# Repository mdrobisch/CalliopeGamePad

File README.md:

# CalliopeGamePad

The CalliopeGamePad adds a gamepad to the Calliope Mini V3 (https://calliope.cc/).
This project is a open source hardware project made with KiCAD (https://www.kicad.org/).
It is intended to be 100% compatible with the CallioGamer of M. Klein @ https://www.hackster.io/MKlein/calliogamer-f57906 . Thanks goes to M. Klein for his wonderful project and his software @ https://github.com/MKleinSB/pxt-calliogamer.

ATTENTION: Due to the connector the Calliope Game Pad Works **only** with Calliope Mini V3.

Here are some differeneces compared to the CallioGamer:

* The CallioGamer production files seems to be broken somehow (at least for my PCB fab of choice). Now you have the freedom to adjust for yours as well.
* Added some additional mounting holes. So you can add a solid body to the board (e.g., cardboard or 3d-print)
* Optional Pull-Up resistors are available. This can also be used for filtering of the buttons with additional capacitors. There is **no need** to solder this for a working gamepad.
* CalliopeGamePad is made in KiCAD 9 (instead of EasyEDA)

You can remix the project and adjust as you like. The hardware is licensed under Creative Commons (CC BY-SA). Please visit the projects of M.Klein and have fun.

## Build your own

Almost all of the big PCB Fabs are able to handle.kicad_pcb files directly. Just upload and let them produce your Calliope Game Pad. In addition you find the gerber fabrication files in the `gerber` directory.

## Software

Please follow the instruction at https://www.hackster.io/MKlein/calliogamer-f57906 . 

You can find the source code of the CallioGamer firmware at https://github.com/MKleinSB/pxt-calliogamer .

## Legal statement

Please read the DISCLAIMER and the LICENSE.

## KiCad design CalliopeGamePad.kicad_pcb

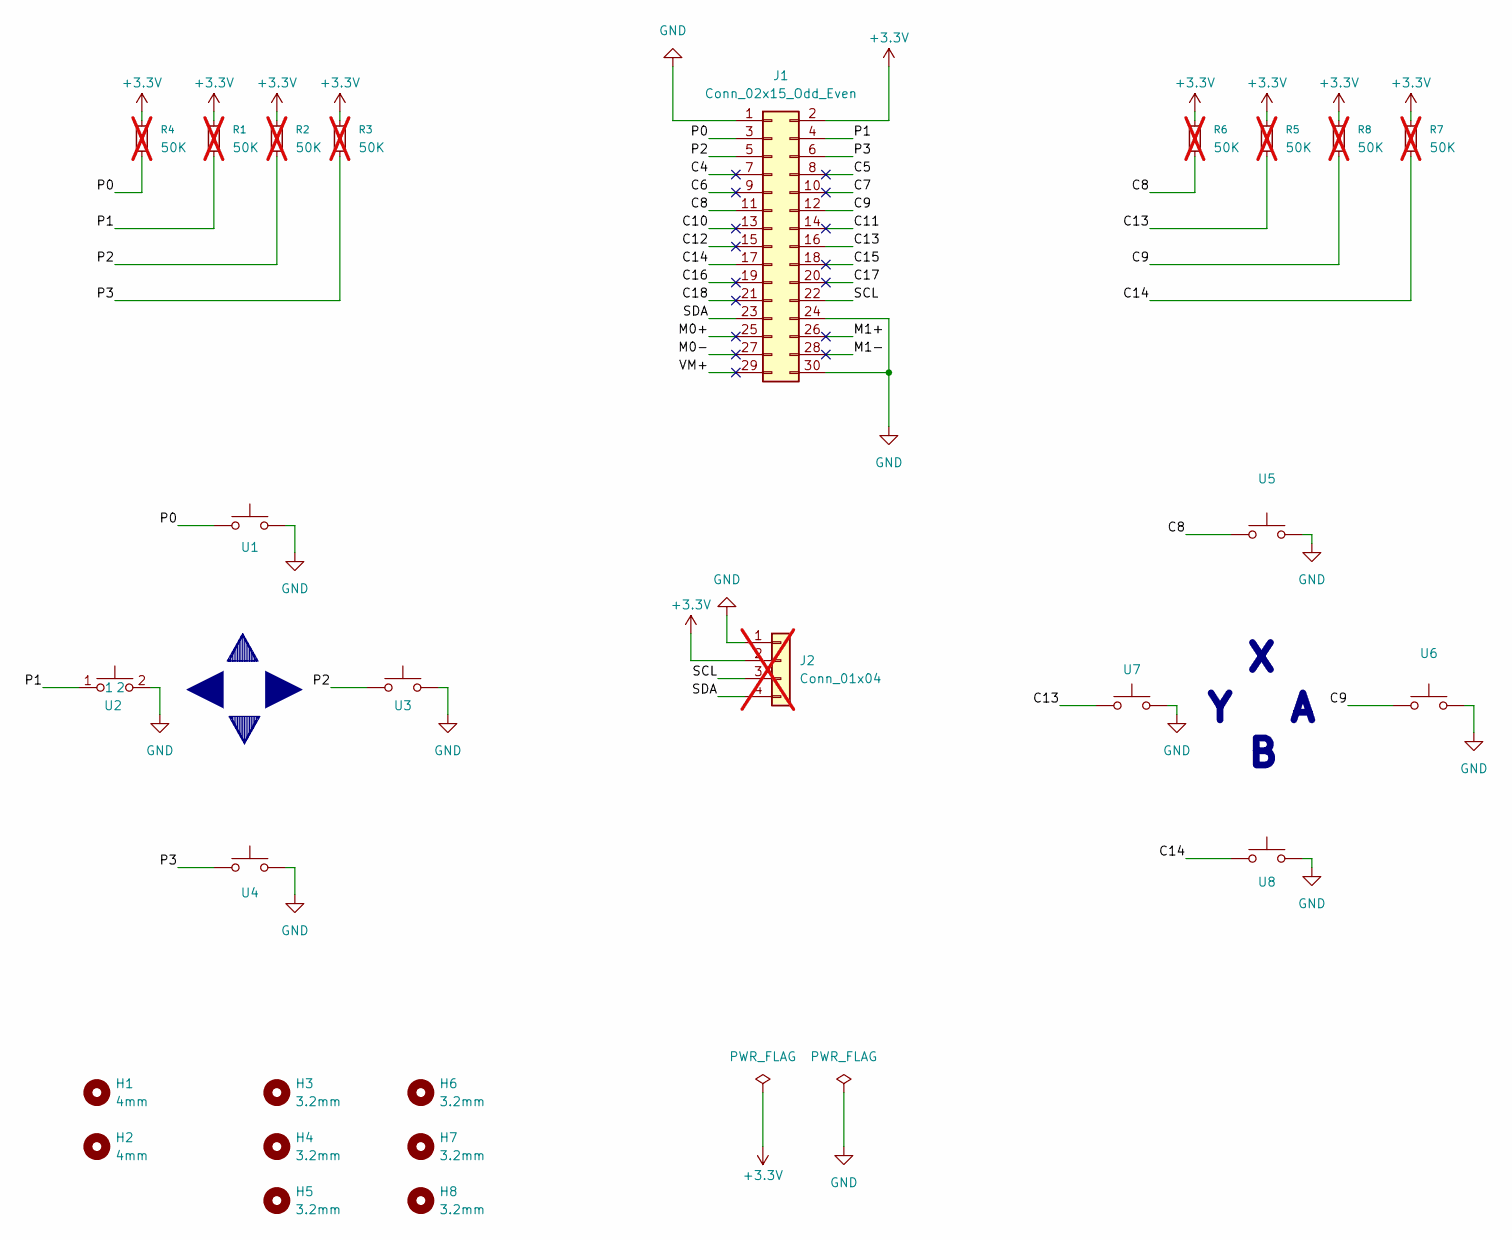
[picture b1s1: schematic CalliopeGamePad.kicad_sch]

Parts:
H1, H2: 4mm; MountingHole_4mm
H3, H4, H5, H6, H7, H8: 3.2mm; MountingHole_3.2mm_M3_DIN965
J1: Conn_02x15_Odd_Even; PinSocket_2x15_P2.54mm_Vertical
J2: Conn_01x04; PinSocket_1x04_P2.54mm_Vertical; not fitted
R1, R2, R3, R4, R5, R6, R7, R8: 50K; R_Axial_DIN0207_L6.3mm_D2.5mm_P15.24mm_Horizontal; not fitted
U1, U2, U3, U4, U5, U6, U7, U8: SW_MEC_5E; SW_PUSH_6mm

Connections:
+3.3V: J1.2, J2.2, R1.1, R2.1, R3.1, R4.1, R5.1, R6.1, R7.1, R8.1
/C4: J1.7
/C5: J1.8
/C6: J1.9
/C7: J1.10
/C8: J1.11, R6.2, U5.1
/C9: J1.12, R8.2, U6.1
/C10: J1.13
/C11: J1.14
/C12: J1.15
/C13: J1.16, R5.2, U7.1
/C14: J1.17, R7.2, U8.1
/C15: J1.18
/C16: J1.19
/C17: J1.20
/C18: J1.21
/M0+: J1.25
/M0-: J1.27
/M1+: J1.26
/M1-: J1.28
/P0: J1.3, R4.2, U1.1
/P1: J1.4, R1.2, U2.1
/P2: J1.5, R2.2, U3.1
/P3: J1.6, R3.2, U4.1
/SCL: J1.22, J2.3
/SDA: J1.23, J2.4
/VM+: J1.29
GND: J1.1, J1.24, J1.30, J2.1, U1.2, U2.2, U3.2, U4.2, U5.2, U6.2, U7.2, U8.2

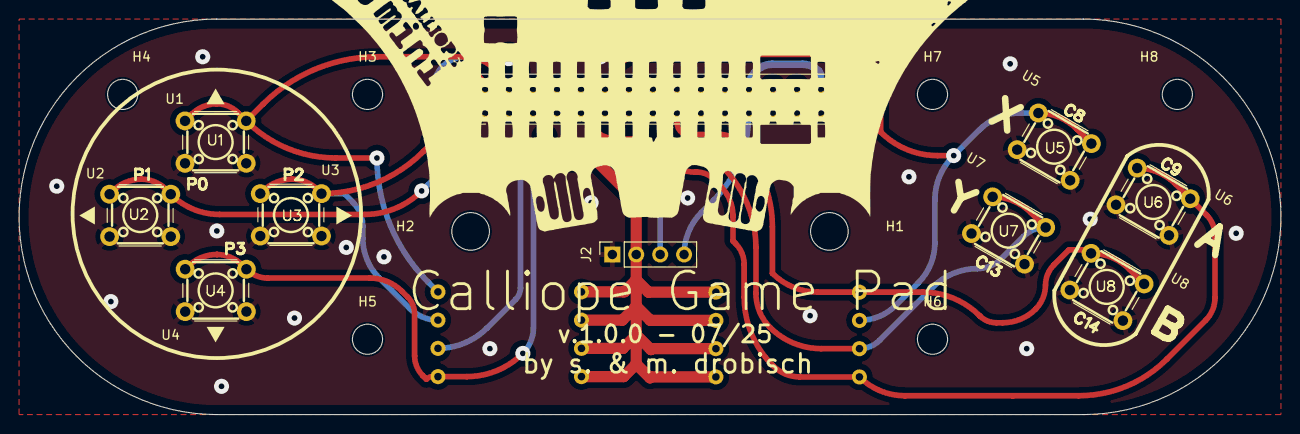
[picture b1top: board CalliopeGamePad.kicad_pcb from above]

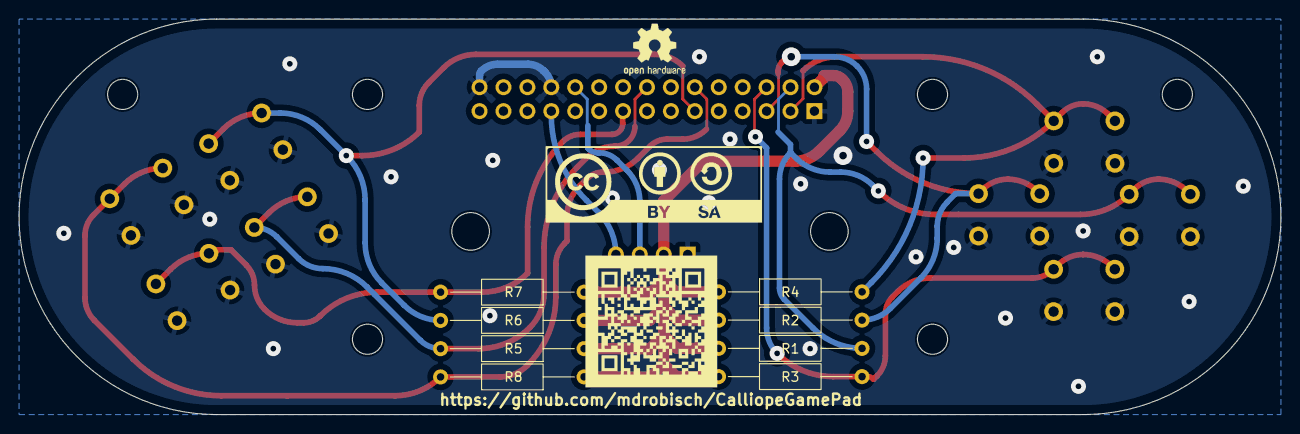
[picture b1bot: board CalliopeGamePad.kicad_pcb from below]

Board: 2 copper layers, 134.0 x 42.0 mm, 26 parts (8 on the bottom side), 12 nets.

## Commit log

2025-07-14 ADD project
2025-07-14 ADD a disclaimer and a README
2025-07-14 IMPROVE the README
2025-07-14 ADD gerber files
2025-07-14 ADD an image
2025-07-15 MAKE the socket a pin header and reroute pin map
2025-07-15 ADD a hint to support only V3
2025-07-15 ADD a hint for using filter
2025-07-15 UPDATE socket footprint in kicad_sch
2025-07-15 UPDATE Gerber and Drill Files
2025-07-15 FIX grammar in readme
